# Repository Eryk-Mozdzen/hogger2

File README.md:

# Two HOG wheel robot Hogger^2

Hogger^2 is mobile robot with two HOG ([Hemispherical Omnidirectional Gimbaled](https://en.wikipedia.org/wiki/Hemispherical_omnidirectional_gimbaled_wheel)) wheels.

- kinematic models were derived by Paweł Joniak in his [engineering thesis](https://kcir.pwr.edu.pl/~mucha/Pracki/Pawel_Joniak_praca_magisterska.pdf) (2014)
- chassis was originally created by Damian Góral in his [engineering thesis](https://kcir.pwr.edu.pl/~mucha/Pracki/Damian_Goral_praca_inzynierska.pdf) (2017)
- control algorithms were designed by Paweł Joniak in his [master thesis](https://kcir.pwr.edu.pl/~mucha/Pracki/Pawel_Joniak_praca_magisterska.pdf) (2017)
- code generation technique was proposed by Jędrzej Boczar in his [master thesis](https://kcir.pwr.edu.pl/~mucha/Pracki/Jedrzej_Boczar_praca_magisterska.pdf) (2019)
- JSON based communication was proposed by Tomasz Lubelski in his [engineering thesis](https://kcir.pwr.edu.pl/~mucha/Pracki/Tomek_Lubelski_praca_inzynierska.pdf) (2023)

## CAD project

CAD files are developed using Onshape [here](https://cad.onshape.com/documents/57202b77900f6c62ca0efc3a/w/393cd826dd9c91d9b304b9f8/e/825e632008c05703f420ee31?renderMode=0&uiState=678308f8541b5276ec2b6970).

## Hardware overview

## Software overview

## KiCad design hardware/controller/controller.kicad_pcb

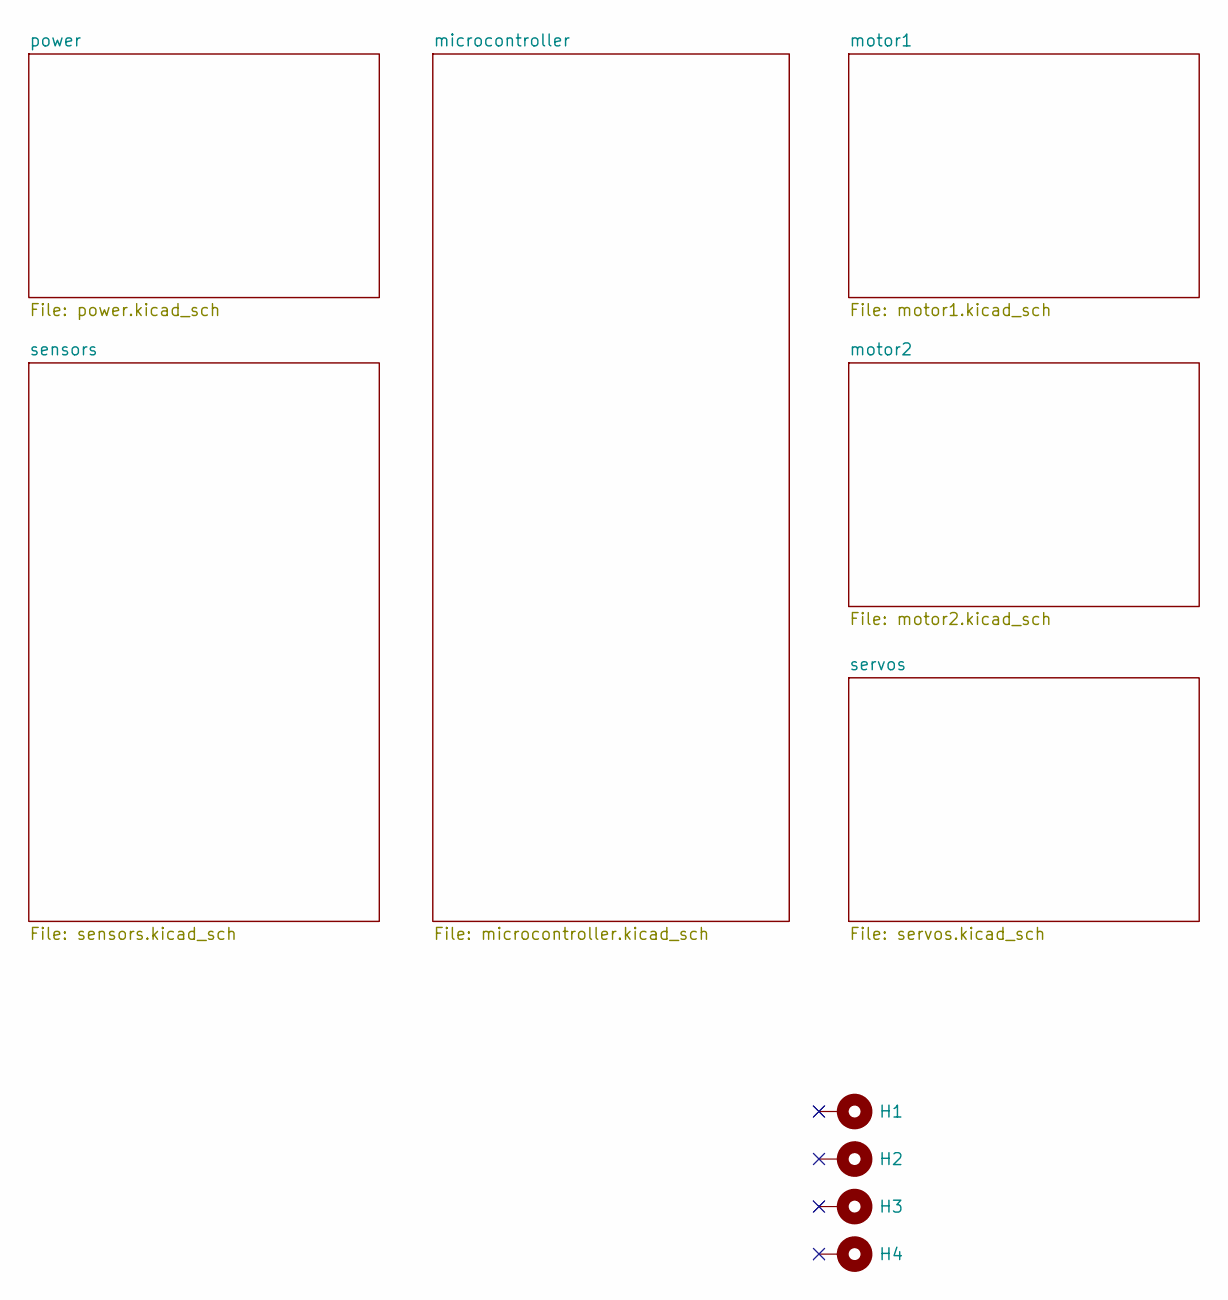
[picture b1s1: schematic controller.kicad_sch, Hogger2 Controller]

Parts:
H1, H2, H3, H4: MountingHole_Pad; MountingHole_3.2mm_M3_Pad_Via

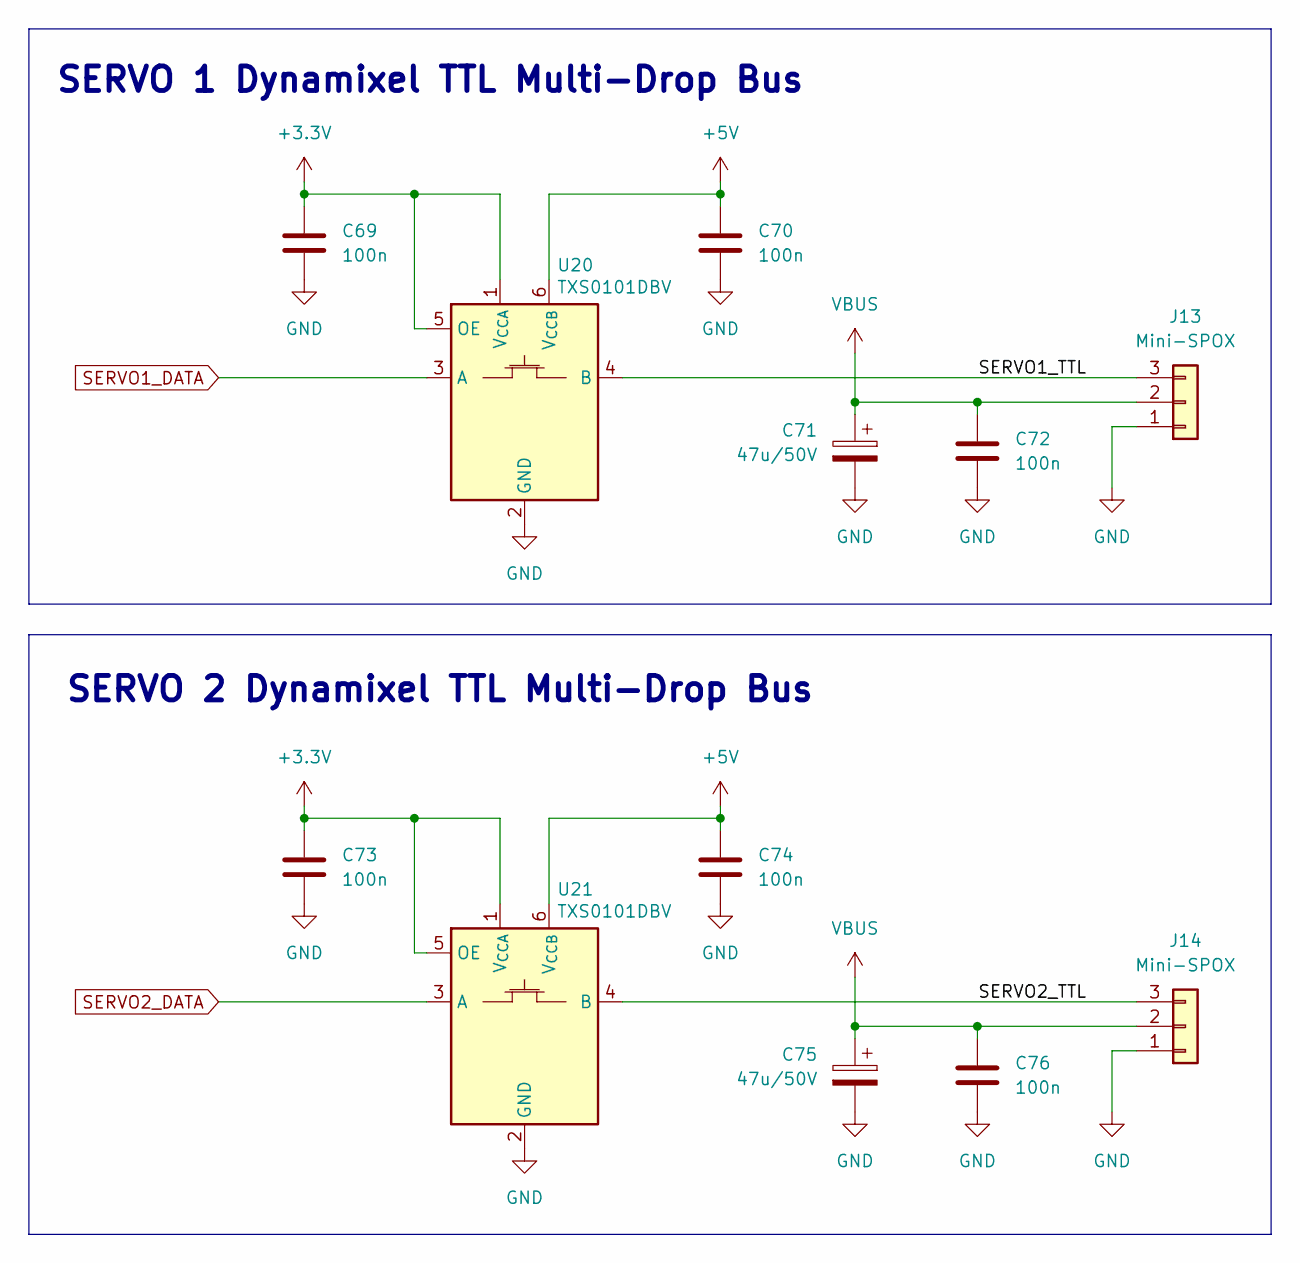
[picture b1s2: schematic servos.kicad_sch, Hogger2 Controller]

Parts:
C69, C70, C72, C73, C74, C76: 100n; C_0603_1608Metric
C71, C75: 47u/50V; CP_Elec_6.3x7.7
J13, J14: Mini-SPOX; Molex-MiniSPOX-22057035-5268
U20, U21: TXS0101DBV; SOT-23-6

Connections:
+3.3V: C69.1, C73.1, U20.1 (V_{CCA}), U20.5 (OE), U21.1 (V_{CCA}), U21.5 (OE); also elsewhere on the board
+5V: C70.1, C74.1, U20.6 (V_{CCB}), U21.6 (V_{CCB}); also elsewhere on the board
/servos/SERVO1_TTL: J13.3, U20.4 (B)
/servos/SERVO2_TTL: J14.3, U21.4 (B)
GND: C69.2, C70.2, C71.2, C72.2, C73.2, C74.2, C75.2, C76.2, J13.1, J14.1, U20.2 (GND), U21.2 (GND); also elsewhere on the board
SERVO1_DATA: U20.3 (A); also elsewhere on the board
SERVO2_DATA: U21.3 (A); also elsewhere on the board
VBUS: C71.1, C72.1, C75.1, C76.1, J13.2, J14.2; also elsewhere on the board

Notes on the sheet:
SERVO 1 Dynamixel TTL Multi-Drop Bus
SERVO 2 Dynamixel TTL Multi-Drop Bus

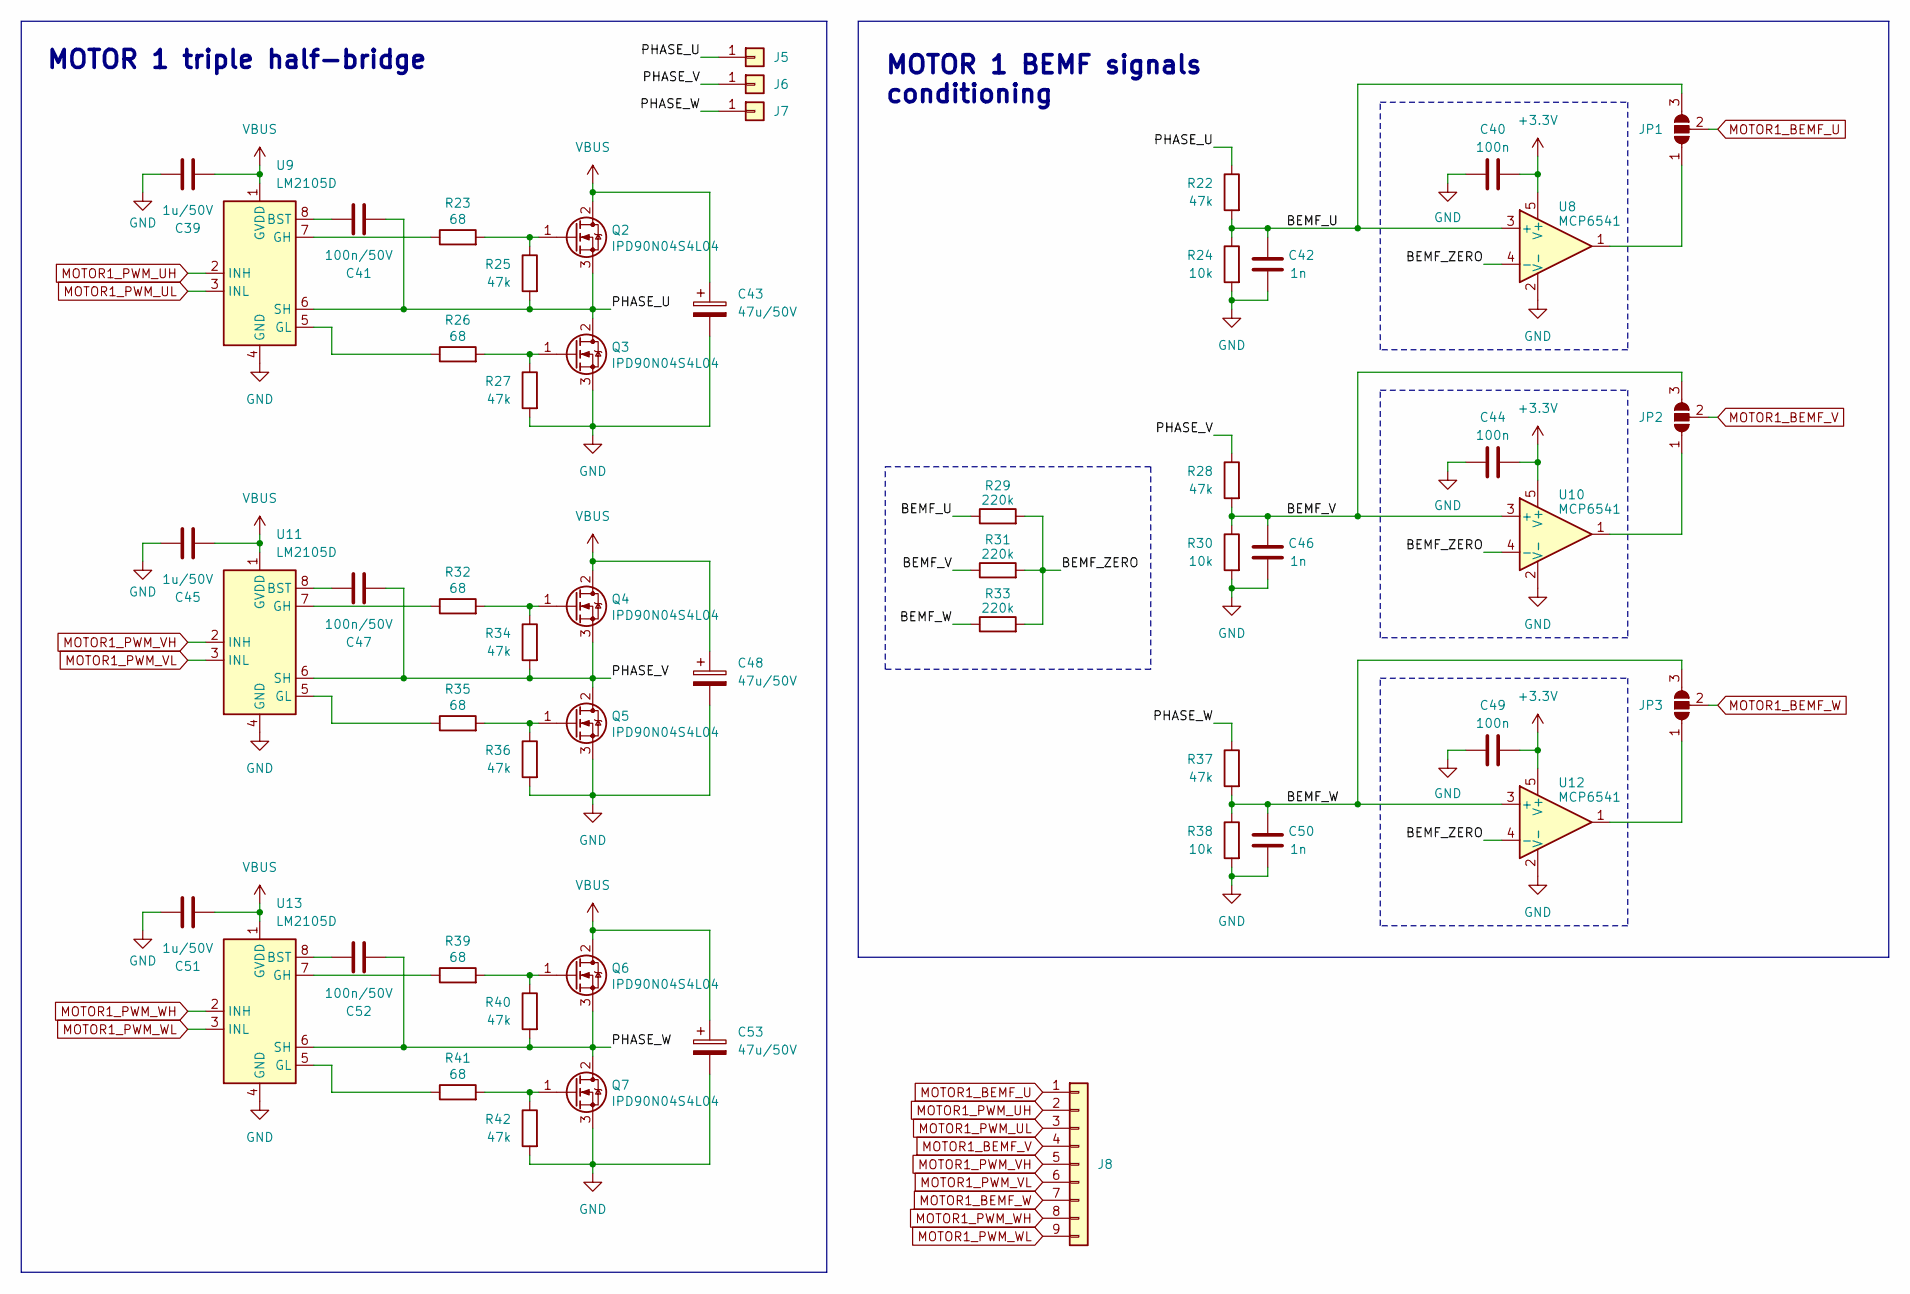
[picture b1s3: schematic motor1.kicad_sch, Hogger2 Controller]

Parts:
C39, C45, C51: 1u/50V; C_0603_1608Metric
C40, C44, C49: 100n; C_0603_1608Metric
C41, C47, C52: 100n/50V; C_0603_1608Metric
C42, C46, C50: 1n; C_0603_1608Metric
C43, C48, C53: 47u/50V; CP_Elec_6.3x7.7
J5, J6, J7: Conn_01x01; SolderWire-2.5sqmm_1x01_D2.4mm_OD4.4mm
J8: Conn_01x09; PinHeader_1x09_P2.54mm_Vertical
JP1, JP2, JP3: SolderJumper_3_Open; SolderJumper-3_P1.3mm_Open_RoundedPad1.0x1.5mm
Q2, Q3, Q4, Q5, Q6, Q7: IPD90N04S4L04; TO-252-2
R22, R25, R27, R28, R34, R36, R37, R40, R42: 47k; R_0603_1608Metric
R23, R26, R32, R35, R39, R41: 68; R_0603_1608Metric
R24, R30, R38: 10k; R_0603_1608Metric
R29, R31, R33: 220k; R_0603_1608Metric
U8, U10, U12: MCP6541; SOT-23-5
U9, U11, U13: LM2105D; SOIC-8_3.9x4.9mm_P1.27mm

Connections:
+3.3V: C40.2, C44.2, C49.2, U8.5 (V+), U10.5 (V+), U12.5 (V+); also elsewhere on the board
/motor1/BEMF_U: C42.1, JP1.3 (B), R22.2, R24.1, R29.1, U8.3 (+)
/motor1/BEMF_V: C46.1, JP2.3 (B), R28.2, R30.1, R31.1, U10.3 (+)
/motor1/BEMF_W: C50.1, JP3.3 (B), R33.1, R37.2, R38.1, U12.3 (+)
/motor1/BEMF_ZERO: R29.2, R31.2, R33.2, U8.4 (-), U10.4 (-), U12.4 (-)
/motor1/PHASE_U: C41.2, J5.1, Q2.3 (S), Q3.2 (D), R22.1, R25.2, U9.6 (SH)
/motor1/PHASE_V: C47.2, J6.1, Q4.3 (S), Q5.2 (D), R28.1, R34.2, U11.6 (SH)
/motor1/PHASE_W: C52.2, J7.1, Q6.3 (S), Q7.2 (D), R37.1, R40.2, U13.6 (SH)
GND: C39.1, C40.1, C42.2, C43.2, C44.1, C45.1, C46.2, C48.2, C49.1, C50.2, C51.1, C53.2, Q3.3 (S), Q5.3 (S), Q7.3 (S), R24.2, R27.2, R30.2, R36.2, R38.2, R42.2, U8.2 (V-), U9.4 (GND), U10.2 (V-), U11.4 (GND), U12.2 (V-), U13.4 (GND); also elsewhere on the board
MOTOR1_BEMF_U: J8.1, JP1.2 (C); also elsewhere on the board
MOTOR1_BEMF_V: J8.4, JP2.2 (C); also elsewhere on the board
MOTOR1_BEMF_W: J8.7, JP3.2 (C); also elsewhere on the board
MOTOR1_PWM_UH: J8.2, U9.2 (INH); also elsewhere on the board
MOTOR1_PWM_UL: J8.3, U9.3 (INL); also elsewhere on the board
MOTOR1_PWM_VH: J8.5, U11.2 (INH); also elsewhere on the board
MOTOR1_PWM_VL: J8.6, U11.3 (INL); also elsewhere on the board
MOTOR1_PWM_WH: J8.8, U13.2 (INH); also elsewhere on the board
MOTOR1_PWM_WL: J8.9, U13.3 (INL); also elsewhere on the board
unnamed: JP1.1 (A), U8.1
unnamed: JP2.1 (A), U10.1
unnamed: JP3.1 (A), U12.1
unnamed: Q2.1 (G), R23.2, R25.1
unnamed: Q3.1 (G), R26.2, R27.1
unnamed: Q4.1 (G), R32.2, R34.1
unnamed: Q5.1 (G), R35.2, R36.1
unnamed: Q6.1 (G), R39.2, R40.1
unnamed: Q7.1 (G), R41.2, R42.1
unnamed: C41.1, U9.8 (BST)
unnamed: R23.1, U9.7 (GH)
unnamed: R26.1, U9.5 (GL)
unnamed: C47.1, U11.8 (BST)
unnamed: R32.1, U11.7 (GH)
unnamed: R35.1, U11.5 (GL)
unnamed: C52.1, U13.8 (BST)
unnamed: R39.1, U13.7 (GH)
unnamed: R41.1, U13.5 (GL)
VBUS: C39.2, C43.1, C45.2, C48.1, C51.2, C53.1, Q2.2 (D), Q4.2 (D), Q6.2 (D), U9.1 (GVDD), U11.1 (GVDD), U13.1 (GVDD); also elsewhere on the board

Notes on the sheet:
MOTOR 1 triple half-bridge
MOTOR 1 BEMF signals conditioning

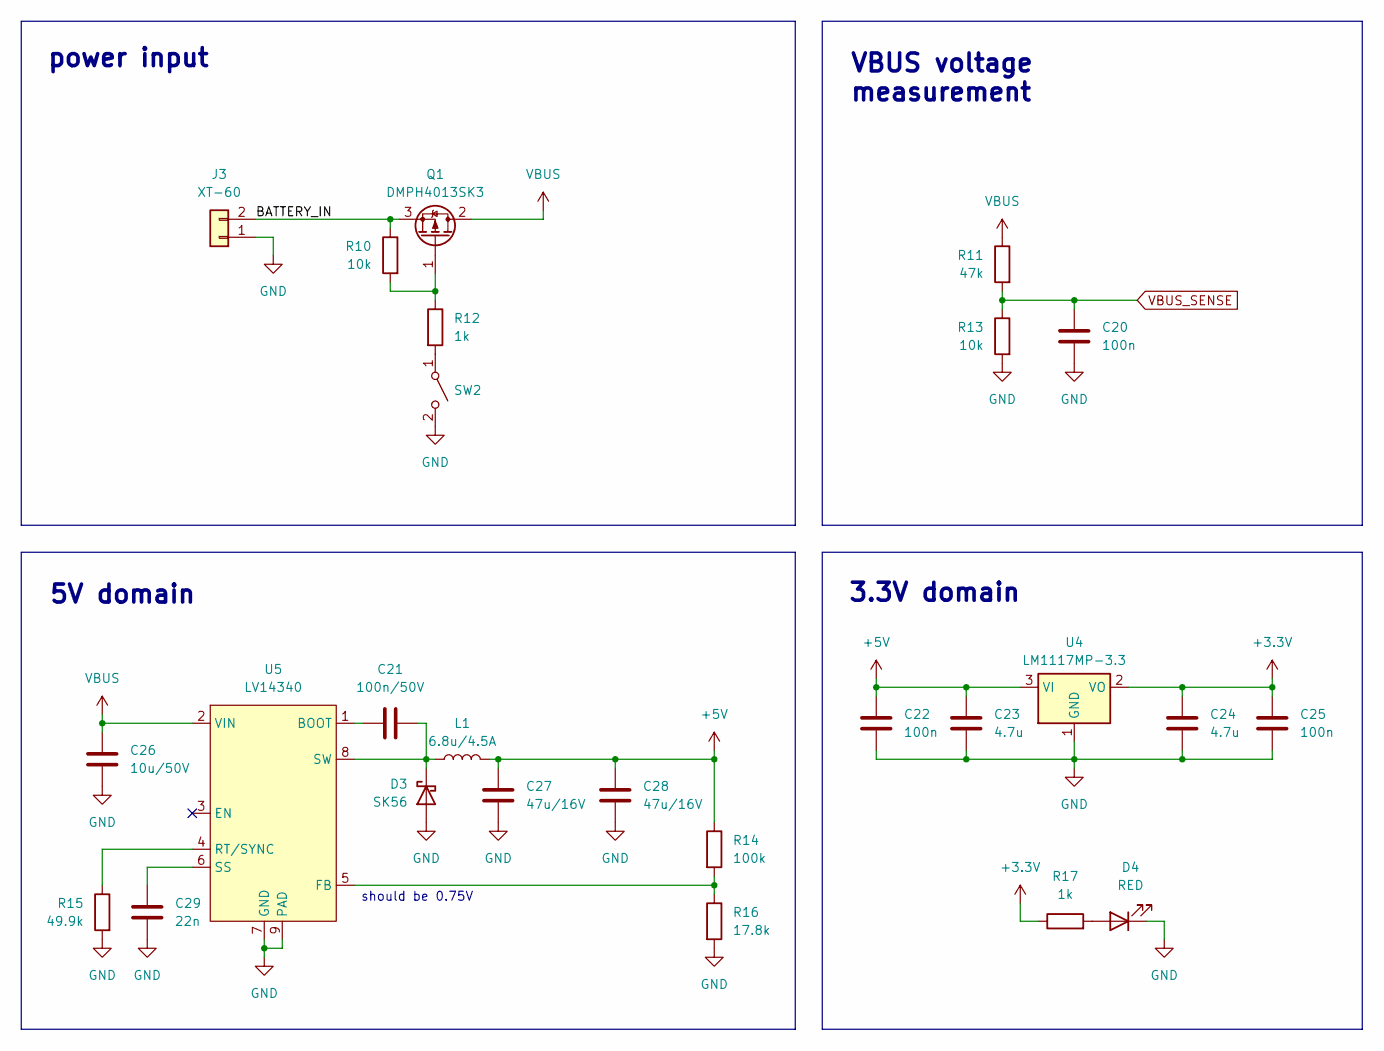
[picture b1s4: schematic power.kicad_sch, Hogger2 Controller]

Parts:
C20, C22, C25: 100n; C_0603_1608Metric
C21: 100n/50V; C_0603_1608Metric
C23, C24: 4.7u; C_0603_1608Metric
C26: 10u/50V; C_1206_3216Metric
C27, C28: 47u/16V; C_1210_3225Metric
C29: 22n; C_0603_1608Metric
D3: SK56; D_SMB
D4: RED; LED_0603_1608Metric
J3: XT-60; XT60PW-M
L1: 6.8u/4.5A; PA4341.XXXNLT
Q1: DMPH4013SK3; TO-252-2
R10, R13: 10k; R_0603_1608Metric
R11: 47k; R_0603_1608Metric
R12, R17: 1k; R_0603_1608Metric
R14: 100k; R_0603_1608Metric
R15: 49.9k; R_0603_1608Metric
R16: 17.8k; R_0603_1608Metric
SW2: SW_SPST; JS102011SAQN
U4: LM1117MP-3.3; SOT-223-3_TabPin2
U5: LV14340

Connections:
+3.3V: C24.1, C25.1, R17.1, U4.2 (VO); also elsewhere on the board
+5V: C22.1, C23.1, C27.1, C28.1, L1.2, R14.1, U4.3 (VI); also elsewhere on the board
/power/BATTERY_IN: J3.2, Q1.3 (S), R10.1
GND: C20.2, C22.2, C23.2, C24.2, C25.2, C26.2, C27.2, C28.2, C29.2, D3.2 (A), D4.1 (K), J3.1, R13.2, R15.2, R16.2, SW2.2 (B), U4.1 (GND), U5.7 (GND), U5.9 (PAD); also elsewhere on the board
unnamed: C21.2, D3.1 (K), L1.1, U5.8 (SW)
unnamed: D4.2 (A), R17.2
unnamed: Q1.1 (G), R10.2, R12.1
unnamed: R12.2, SW2.1 (A)
unnamed: C21.1, U5.1 (BOOT)
unnamed: R14.2, R16.1, U5.5 (FB)
unnamed: R15.1, U5.4 (RT/SYNC)
unnamed: C29.1, U5.6 (SS)
VBUS: C26.1, Q1.2 (D), R11.1, U5.2 (VIN); also elsewhere on the board
VBUS_SENSE: C20.1, R11.2, R13.1; also elsewhere on the board

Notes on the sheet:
5V domain
VBUS voltage measurement
3.3V domain
should be 0.75V
power input

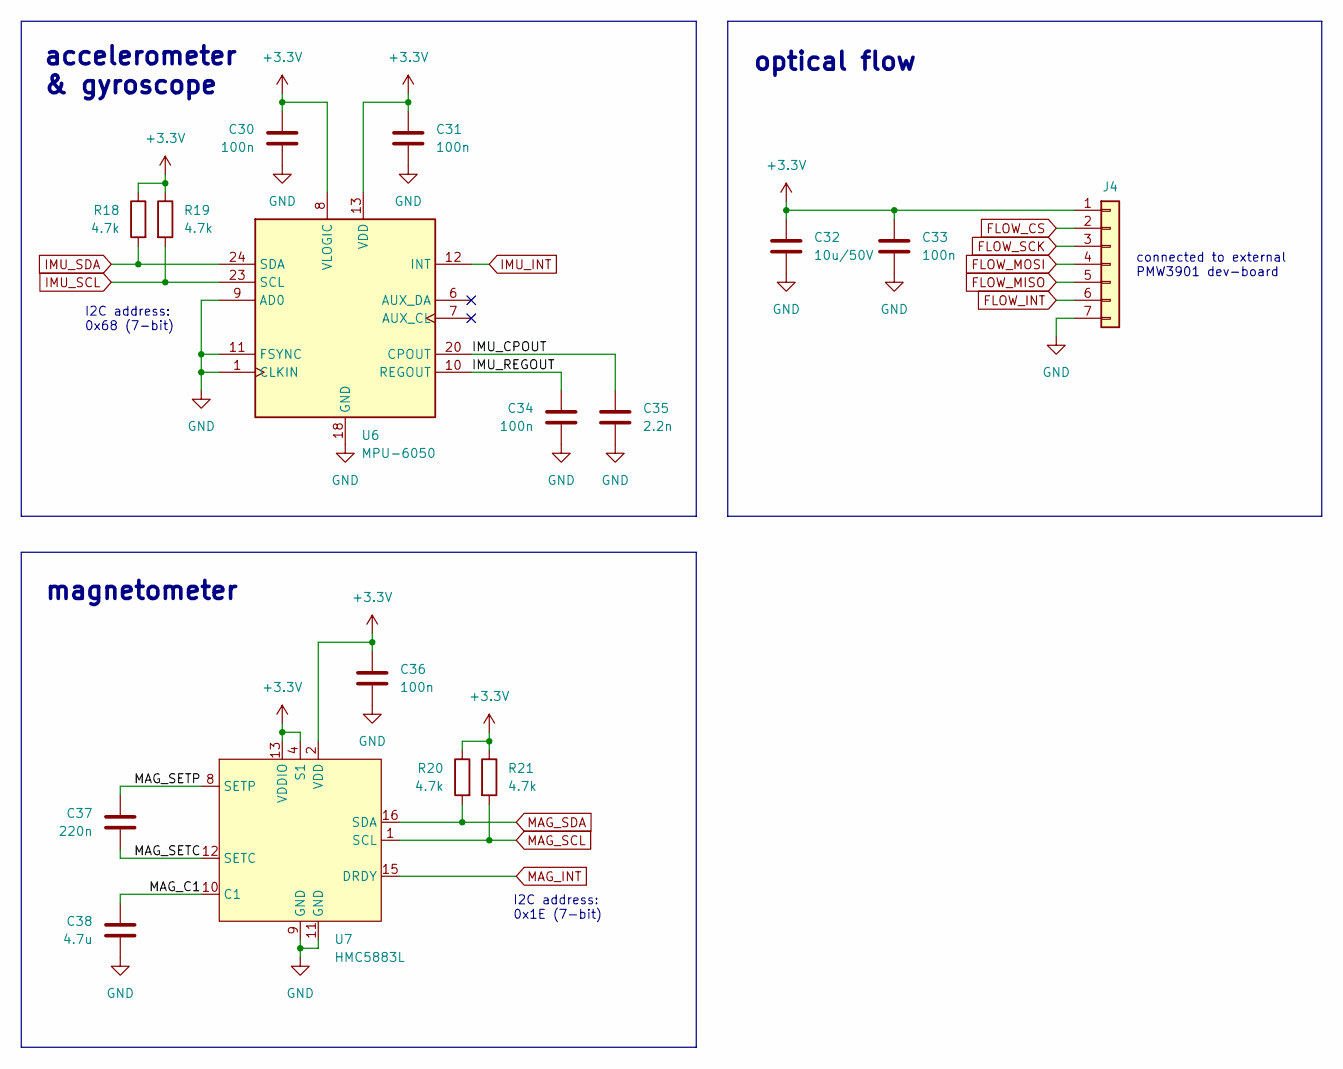
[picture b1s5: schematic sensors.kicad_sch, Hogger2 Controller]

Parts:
C30, C31, C33, C34, C36: 100n; C_0603_1608Metric
C32: 10u/50V; C_1206_3216Metric
C35: 2.2n; C_0603_1608Metric
C37: 220n; C_0603_1608Metric
C38: 4.7u; C_0603_1608Metric
J4: Conn_01x07; PinHeader_1x07_P2.54mm_Horizontal
R18, R19, R20, R21: 4.7k; R_0603_1608Metric
U6: MPU-6050; MPU6050_handsolder
U7: HMC5883L; HMC5883L_handsolder

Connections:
+3.3V: C30.1, C31.1, C32.1, C33.1, C36.1, J4.1, R18.1, R19.1, R20.1, R21.1, U6.8 (VLOGIC), U6.13 (VDD), U7.2 (VDD), U7.4 (S1), U7.13 (VDDIO); also elsewhere on the board
/sensors/IMU_CPOUT: C35.1, U6.20 (CPOUT)
/sensors/IMU_REGOUT: C34.1, U6.10 (REGOUT)
/sensors/MAG_C1: C38.1, U7.10 (C1)
/sensors/MAG_SETC: C37.2, U7.12 (SETC)
/sensors/MAG_SETP: C37.1, U7.8 (SETP)
FLOW_CS: J4.2; also elsewhere on the board
FLOW_INT: J4.6; also elsewhere on the board
FLOW_MISO: J4.5; also elsewhere on the board
FLOW_MOSI: J4.4; also elsewhere on the board
FLOW_SCK: J4.3; also elsewhere on the board
GND: C30.2, C31.2, C32.2, C33.2, C34.2, C35.2, C36.2, C38.2, J4.7, U6.1 (CLKIN), U6.9 (AD0), U6.11 (FSYNC), U6.18 (GND), U7.9 (GND), U7.11 (GND); also elsewhere on the board
IMU_INT: U6.12 (INT); also elsewhere on the board
IMU_SCL: R19.2, U6.23 (SCL); also elsewhere on the board
IMU_SDA: R18.2, U6.24 (SDA); also elsewhere on the board
MAG_INT: U7.15 (DRDY); also elsewhere on the board
MAG_SCL: R21.2, U7.1 (SCL); also elsewhere on the board
MAG_SDA: R20.2, U7.16 (SDA); also elsewhere on the board

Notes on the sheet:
accelerometer & gyroscope
connected to external PMW3901 dev-board
I2C address: 0x68 (7-bit)
magnetometer
optical flow
I2C address: 0x1E (7-bit)

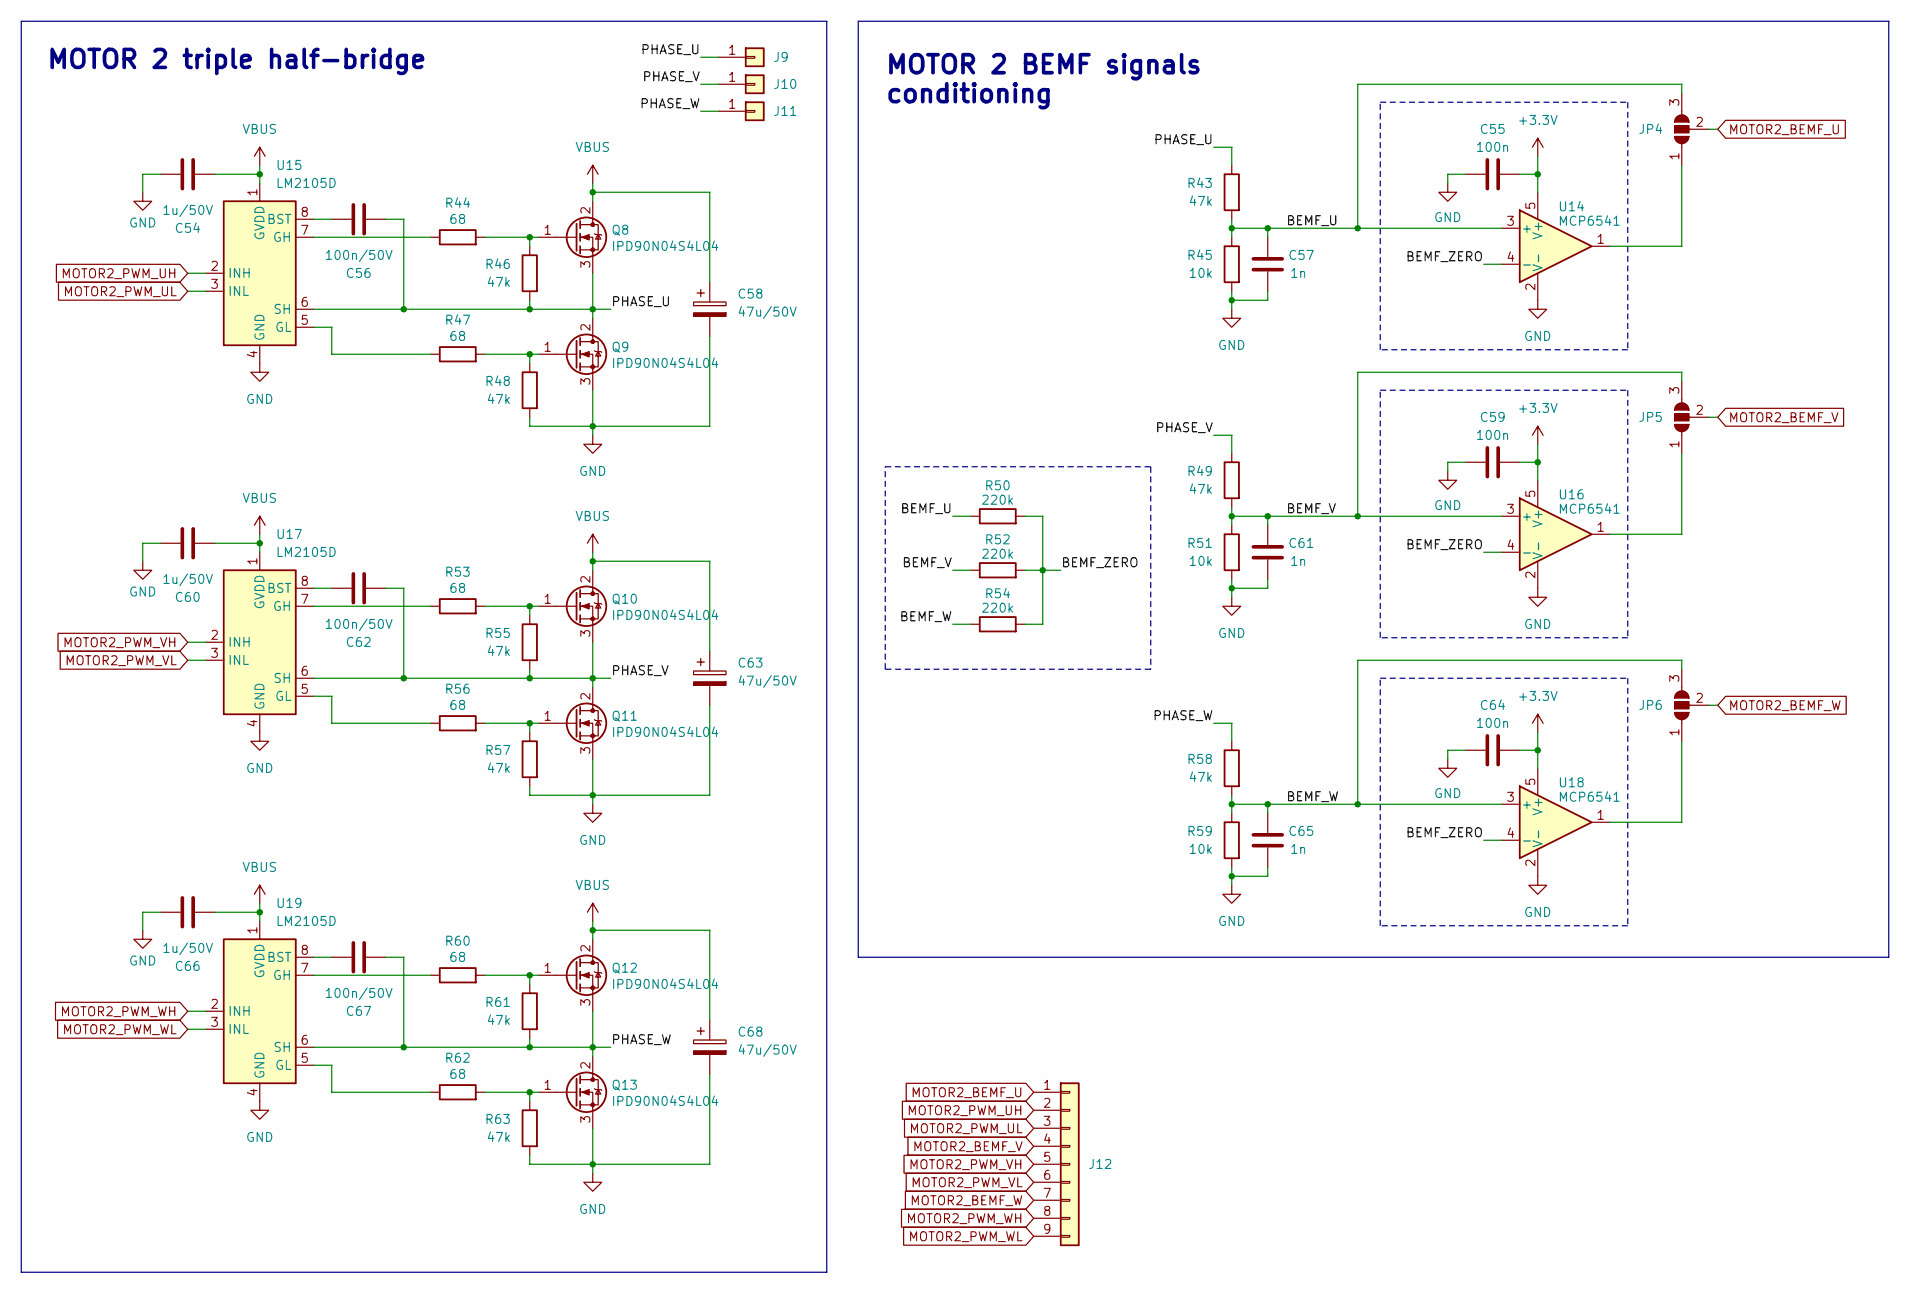
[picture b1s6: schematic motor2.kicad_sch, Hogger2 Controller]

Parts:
C54, C60, C66: 1u/50V; C_0603_1608Metric
C55, C59, C64: 100n; C_0603_1608Metric
C56, C62, C67: 100n/50V; C_0603_1608Metric
C57, C61, C65: 1n; C_0603_1608Metric
C58, C63, C68: 47u/50V; CP_Elec_6.3x7.7
J9, J10, J11: Conn_01x01; SolderWire-2.5sqmm_1x01_D2.4mm_OD4.4mm
J12: Conn_01x09; PinHeader_1x09_P2.54mm_Vertical
JP4, JP5, JP6: SolderJumper_3_Open; SolderJumper-3_P1.3mm_Open_RoundedPad1.0x1.5mm
Q8, Q9, Q10, Q11, Q12, Q13: IPD90N04S4L04; TO-252-2
R43, R46, R48, R49, R55, R57, R58, R61, R63: 47k; R_0603_1608Metric
R44, R47, R53, R56, R60, R62: 68; R_0603_1608Metric
R45, R51, R59: 10k; R_0603_1608Metric
R50, R52, R54: 220k; R_0603_1608Metric
U14, U16, U18: MCP6541; SOT-23-5
U15, U17, U19: LM2105D; SOIC-8_3.9x4.9mm_P1.27mm

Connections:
+3.3V: C55.2, C59.2, C64.2, U14.5 (V+), U16.5 (V+), U18.5 (V+); also elsewhere on the board
/motor2/BEMF_U: C57.1, JP4.3 (B), R43.2, R45.1, R50.1, U14.3 (+)
/motor2/BEMF_V: C61.1, JP5.3 (B), R49.2, R51.1, R52.1, U16.3 (+)
/motor2/BEMF_W: C65.1, JP6.3 (B), R54.1, R58.2, R59.1, U18.3 (+)
/motor2/BEMF_ZERO: R50.2, R52.2, R54.2, U14.4 (-), U16.4 (-), U18.4 (-)
/motor2/PHASE_U: C56.2, J9.1, Q8.3 (S), Q9.2 (D), R43.1, R46.2, U15.6 (SH)
/motor2/PHASE_V: C62.2, J10.1, Q10.3 (S), Q11.2 (D), R49.1, R55.2, U17.6 (SH)
/motor2/PHASE_W: C67.2, J11.1, Q12.3 (S), Q13.2 (D), R58.1, R61.2, U19.6 (SH)
GND: C54.1, C55.1, C57.2, C58.2, C59.1, C60.1, C61.2, C63.2, C64.1, C65.2, C66.1, C68.2, Q9.3 (S), Q11.3 (S), Q13.3 (S), R45.2, R48.2, R51.2, R57.2, R59.2, R63.2, U14.2 (V-), U15.4 (GND), U16.2 (V-), U17.4 (GND), U18.2 (V-), U19.4 (GND); also elsewhere on the board
MOTOR2_BEMF_U: J12.1, JP4.2 (C); also elsewhere on the board
MOTOR2_BEMF_V: J12.4, JP5.2 (C); also elsewhere on the board
MOTOR2_BEMF_W: J12.7, JP6.2 (C); also elsewhere on the board
MOTOR2_PWM_UH: J12.2, U15.2 (INH); also elsewhere on the board
MOTOR2_PWM_UL: J12.3, U15.3 (INL); also elsewhere on the board
MOTOR2_PWM_VH: J12.5, U17.2 (INH); also elsewhere on the board
MOTOR2_PWM_VL: J12.6, U17.3 (INL); also elsewhere on the board
MOTOR2_PWM_WH: J12.8, U19.2 (INH); also elsewhere on the board
MOTOR2_PWM_WL: J12.9, U19.3 (INL); also elsewhere on the board
unnamed: JP4.1 (A), U14.1
unnamed: JP5.1 (A), U16.1
unnamed: JP6.1 (A), U18.1
unnamed: Q8.1 (G), R44.2, R46.1
unnamed: Q9.1 (G), R47.2, R48.1
unnamed: Q10.1 (G), R53.2, R55.1
unnamed: Q11.1 (G), R56.2, R57.1
unnamed: Q12.1 (G), R60.2, R61.1
unnamed: Q13.1 (G), R62.2, R63.1
unnamed: C56.1, U15.8 (BST)
unnamed: R44.1, U15.7 (GH)
unnamed: R47.1, U15.5 (GL)
unnamed: C62.1, U17.8 (BST)
unnamed: R53.1, U17.7 (GH)
unnamed: R56.1, U17.5 (GL)
unnamed: C67.1, U19.8 (BST)
unnamed: R60.1, U19.7 (GH)
unnamed: R62.1, U19.5 (GL)
VBUS: C54.2, C58.1, C60.2, C63.1, C66.2, C68.1, Q8.2 (D), Q10.2 (D), Q12.2 (D), U15.1 (GVDD), U17.1 (GVDD), U19.1 (GVDD); also elsewhere on the board

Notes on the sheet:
MOTOR 2 BEMF signals conditioning
MOTOR 2 triple half-bridge

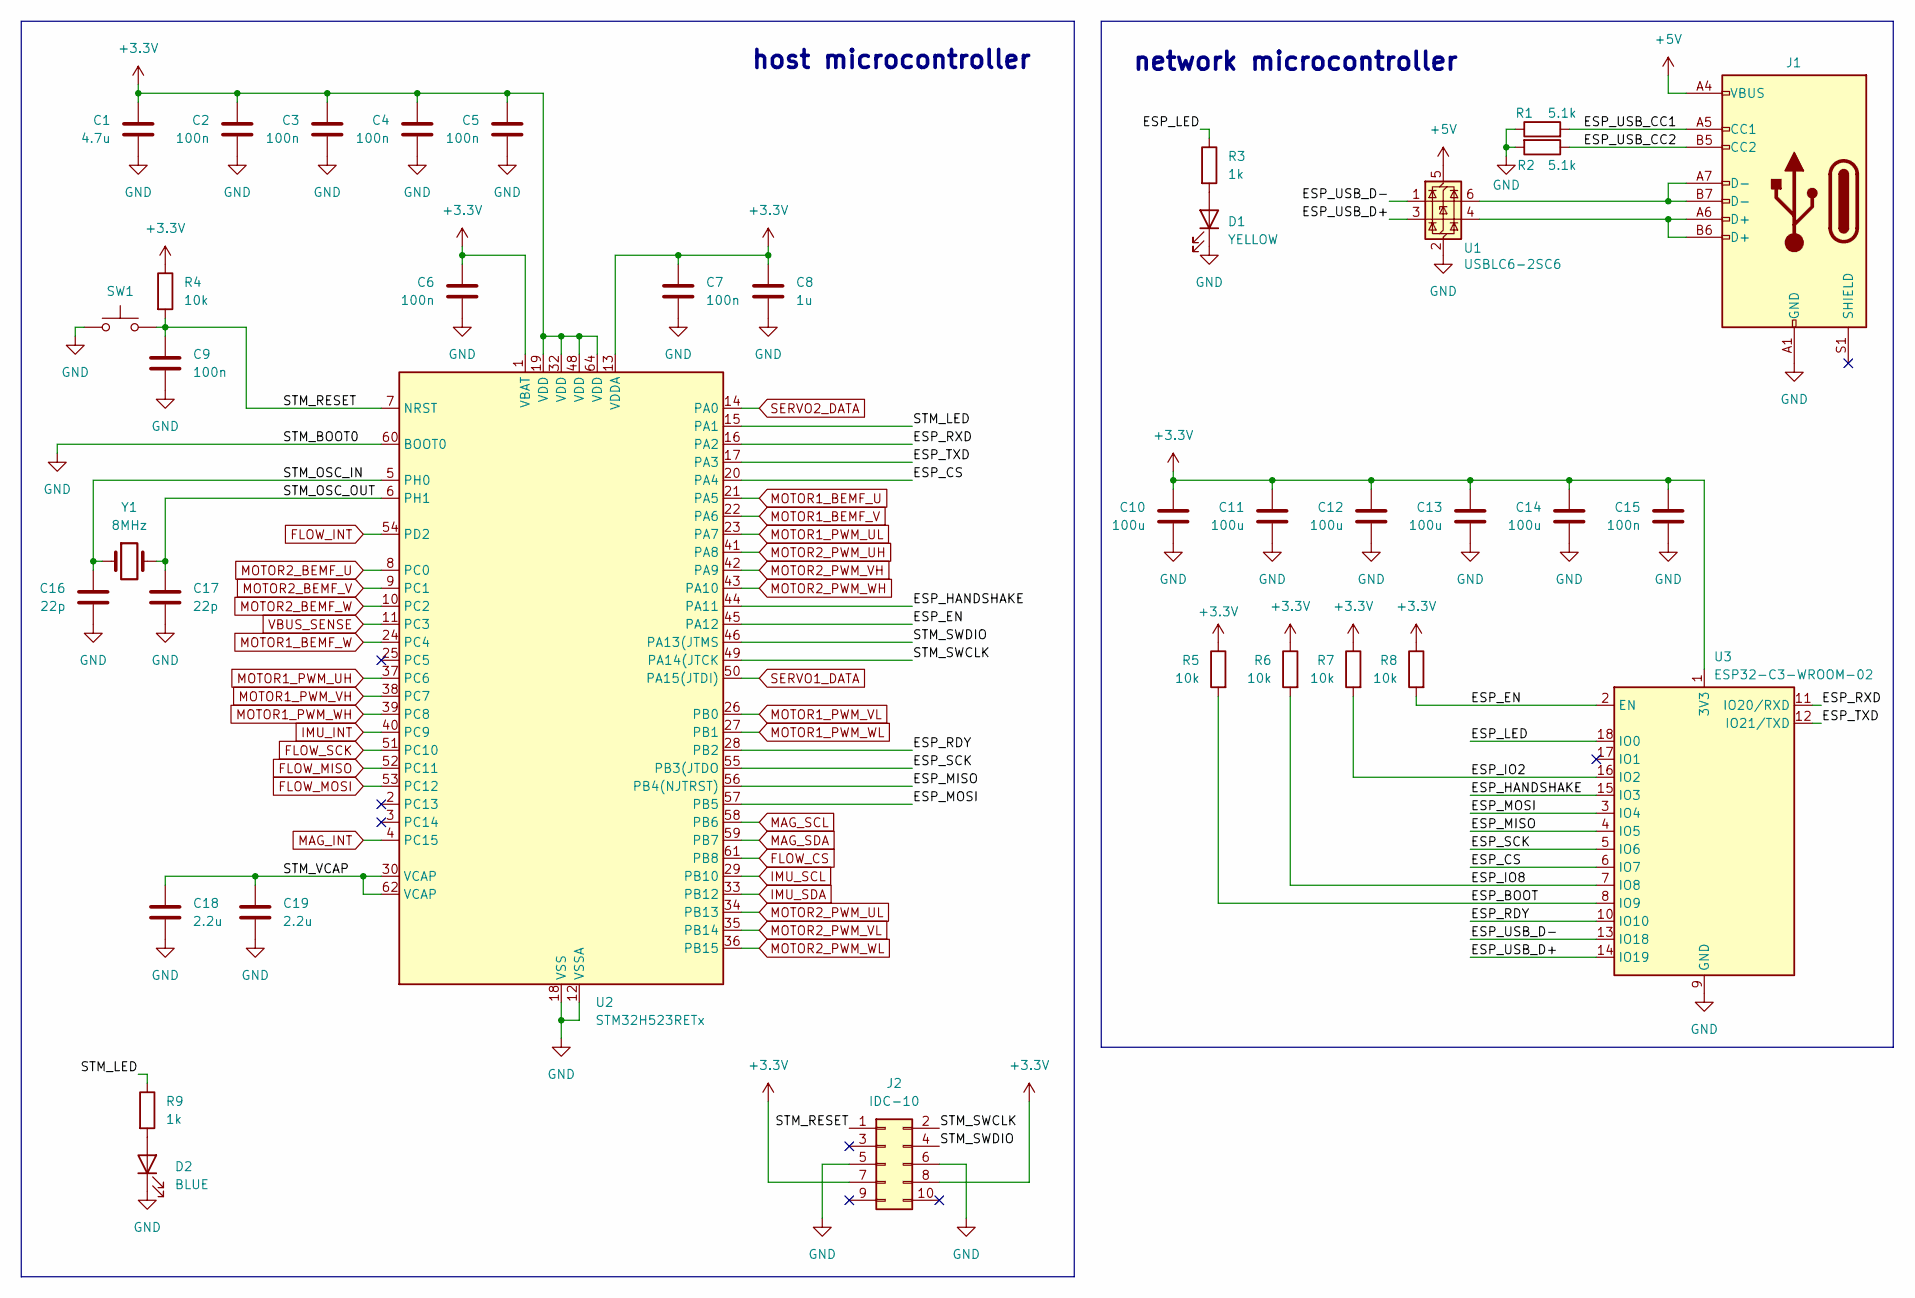
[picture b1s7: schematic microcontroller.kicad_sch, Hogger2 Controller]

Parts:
C1: 4.7u; C_0603_1608Metric
C2, C3, C4, C5, C6, C7, C9, C15: 100n; C_0603_1608Metric
C8: 1u; C_0603_1608Metric
C10, C11, C12, C13, C14: 100u; C_1206_3216Metric
C16, C17: 22p; C_0603_1608Metric
C18, C19: 2.2u; C_0603_1608Metric
D1: YELLOW; LED_0603_1608Metric
D2: BLUE; LED_0603_1608Metric
J1: USB_C_Receptacle_USB2.0_14P; USB_C_Receptacle_GCT_USB4085
J2: IDC-10; IDC-Header_2x05_P2.54mm_Vertical
R1, R2: 5.1k; R_0603_1608Metric
R3, R9: 1k; R_0603_1608Metric
R4, R5, R6, R7, R8: 10k; R_0603_1608Metric
SW1: SW_Push; spst_6x3mm
U1: USBLC6-2SC6; SOT-23-6
U2: STM32H523RETx; LQFP-64_10x10mm_P0.5mm
U3: ESP32-C3-WROOM-02
Y1: 8MHz; Crystal_SMD_5032-2Pin_5.0x3.2mm

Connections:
+3.3V: C1.1, C2.1, C3.1, C4.1, C5.1, C6.1, C7.1, C8.1, C10.1, C11.1, C12.1, C13.1, C14.1, C15.1, J2.7, J2.8, R4.1, R5.1, R6.1, R7.1, R8.1, U2.1 (VBAT), U2.13 (VDDA), U2.19 (VDD), U2.32 (VDD), U2.48 (VDD), U2.64 (VDD), U3.1 (3V3); also elsewhere on the board
+5V: J1.A4 (VBUS), J1.A9 (VBUS), J1.B4 (VBUS), J1.B9 (VBUS), U1.5 (VBUS); also elsewhere on the board
/microcontroller/ESP_BOOT: R5.2, U3.8 (IO9)
/microcontroller/ESP_CS: U2.20 (PA4), U3.6 (IO7)
/microcontroller/ESP_EN: R8.2, U2.45 (PA12), U3.2 (EN)
/microcontroller/ESP_HANDSHAKE: U2.44 (PA11), U3.15 (IO3)
/microcontroller/ESP_IO2: R7.2, U3.16 (IO2)
/microcontroller/ESP_IO8: R6.2, U3.7 (IO8)
/microcontroller/ESP_LED: R3.1, U3.18 (IO0)
/microcontroller/ESP_MISO: U2.56 (PB4(NJTRST)), U3.4 (IO5)
/microcontroller/ESP_MOSI: U2.57 (PB5), U3.3 (IO4)
/microcontroller/ESP_RDY: U2.28 (PB2), U3.10 (IO10)
/microcontroller/ESP_RXD: U2.16 (PA2), U3.11 (IO20/RXD)
/microcontroller/ESP_SCK: U2.55 (PB3(JTDO), U3.5 (IO6)
/microcontroller/ESP_TXD: U2.17 (PA3), U3.12 (IO21/TXD)
/microcontroller/ESP_USB_CC1: J1.A5 (CC1), R1.2
/microcontroller/ESP_USB_CC2: J1.B5 (CC2), R2.1
/microcontroller/ESP_USB_D+: U1.3 (I/O2), U3.14 (IO19)
/microcontroller/ESP_USB_D-: U1.1 (I/O1), U3.13 (IO18)
/microcontroller/STM_LED: R9.1, U2.15 (PA1)
/microcontroller/STM_OSC_IN: C16.1, U2.5 (PH0), Y1.1
/microcontroller/STM_OSC_OUT: C17.1, U2.6 (PH1), Y1.2
/microcontroller/STM_RESET: C9.1, J2.1, R4.2, SW1.2, U2.7 (NRST)
/microcontroller/STM_SWCLK: J2.2, U2.49 (PA14(JTCK)
/microcontroller/STM_SWDIO: J2.4, U2.46 (PA13(JTMS)
/microcontroller/STM_VCAP: C18.1, C19.1, U2.30 (VCAP), U2.62 (VCAP)
FLOW_CS: U2.61 (PB8); also elsewhere on the board
FLOW_INT: U2.54 (PD2); also elsewhere on the board
FLOW_MISO: U2.52 (PC11); also elsewhere on the board
FLOW_MOSI: U2.53 (PC12); also elsewhere on the board
FLOW_SCK: U2.51 (PC10); also elsewhere on the board
GND: C1.2, C2.2, C3.2, C4.2, C5.2, C6.2, C7.2, C8.2, C9.2, C10.2, C11.2, C12.2, C13.2, C14.2, C15.2, C16.2, C17.2, C18.2, C19.2, D1.1 (K), D2.1 (K), J1.A1 (GND), J1.A12 (GND), J1.B1 (GND), J1.B12 (GND), J2.5, J2.6, R1.1, R2.2, SW1.1, U1.2 (GND), U2.12 (VSSA), U2.18 (VSS), U2.31 (VSS), U2.47 (VSS), U2.60 (BOOT0), U2.63 (VSS), U3.9 (GND), U3.19 (GND); also elsewhere on the board
IMU_INT: U2.40 (PC9); also elsewhere on the board
IMU_SCL: U2.29 (PB10); also elsewhere on the board
IMU_SDA: U2.33 (PB12); also elsewhere on the board
MAG_INT: U2.4 (PC15); also elsewhere on the board
MAG_SCL: U2.58 (PB6); also elsewhere on the board
MAG_SDA: U2.59 (PB7); also elsewhere on the board
MOTOR1_BEMF_U: U2.21 (PA5); also elsewhere on the board
MOTOR1_BEMF_V: U2.22 (PA6); also elsewhere on the board
MOTOR1_BEMF_W: U2.24 (PC4); also elsewhere on the board
MOTOR1_PWM_UH: U2.37 (PC6); also elsewhere on the board
MOTOR1_PWM_UL: U2.23 (PA7); also elsewhere on the board
MOTOR1_PWM_VH: U2.38 (PC7); also elsewhere on the board
MOTOR1_PWM_VL: U2.26 (PB0); also elsewhere on the board
MOTOR1_PWM_WH: U2.39 (PC8); also elsewhere on the board
MOTOR1_PWM_WL: U2.27 (PB1); also elsewhere on the board
MOTOR2_BEMF_U: U2.8 (PC0); also elsewhere on the board
MOTOR2_BEMF_V: U2.9 (PC1); also elsewhere on the board
MOTOR2_BEMF_W: U2.10 (PC2); also elsewhere on the board
MOTOR2_PWM_UH: U2.41 (PA8); also elsewhere on the board
MOTOR2_PWM_UL: U2.34 (PB13); also elsewhere on the board
MOTOR2_PWM_VH: U2.42 (PA9); also elsewhere on the board
MOTOR2_PWM_VL: U2.35 (PB14); also elsewhere on the board
MOTOR2_PWM_WH: U2.43 (PA10); also elsewhere on the board
MOTOR2_PWM_WL: U2.36 (PB15); also elsewhere on the board
unnamed: D1.2 (A), R3.2
unnamed: D2.2 (A), R9.2
unnamed: J1.A6 (D+), J1.B6 (D+), U1.4 (I/O2)
unnamed: J1.A7 (D-), J1.B7 (D-), U1.6 (I/O1)
SERVO1_DATA: U2.50 (PA15(JTDI)); also elsewhere on the board
SERVO2_DATA: U2.14 (PA0); also elsewhere on the board
VBUS_SENSE: U2.11 (PC3); also elsewhere on the board

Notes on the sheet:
network microcontroller
host microcontroller
